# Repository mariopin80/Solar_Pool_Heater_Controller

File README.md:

# Solar Pool Heater Controller

[Português (Brasil)](README.pt-BR.md)

Designed by Mario Pin (PU2PTU). The controller compares water temperatures at the pool and the solar collector and switches the heating pump according to the temperature difference. A separate relay runs the filtration pump on a schedule. Later firmware revisions add manual pump modes, scheduled heating-loop circulation, and a serial Bluetooth interface.

## Hardware

| Board | Controller and clock | Firmware |
| --- | --- | --- |
| [MPS01 1.0](hardware/MPS01/1.0) | ATmega328P at 16 MHz and DS1307 | Historical PCB. This revision reverses SDA and SCL. |
| [MPS01 1.1](hardware/MPS01/1.1) | ATmega328P at 16 MHz and DS1307 | Target board for the archived AVR firmware. Corrected I²C routing. |
| [MPS02 2.0](hardware/MPS02/2.0) | ESP32-WROOM-32D and DS3231M | KiCad design only. This revision stayed at the design stage. |

The MPS01 1.1 is the target for the 13 historical firmware versions and the 0.4.0 beta. The MPS01 uses two 10 kΩ NTC probes, a parallel 16×2 LCD, three push buttons and separate relays for the heating and filtration pumps. The hardware guide includes the Arduino pinout, connector assignments and the sensor-label discrepancy between the MPS01 schematics and sketches. [Hardware and assembly guide](docs/hardware.md) · [Original parts list](docs/BOM.xlsx)

## Firmware

The `v0.4.0-beta` adds a responsive three-button panel, probe and RTC diagnostics, validated EEPROM settings and an optional Bluetooth UART protocol for an app. The MPS01 1.1 pin mapping is unchanged. Download the complete source archive to compile the beta.

- [Beta installation and operating guide](docs/firmware.md)
- [Bluetooth protocol v1](docs/bluetooth.md)
- [Firmware review and commercial feature comparison (PT-BR)](docs/firmware-review.pt-BR.md)
- [Changes by version](CHANGELOG.md)
- [GitHub releases](https://github.com/mariopin80/Aquecedor_piscina/releases)
- [MPS01 PCB test sketch](examples/teste_PCB)

The historical releases retain their original sketches at `firmware/PoolHeater/PoolHeater.ino`. The beta uses that same Arduino entry point with its companion source files in the sketch folder.

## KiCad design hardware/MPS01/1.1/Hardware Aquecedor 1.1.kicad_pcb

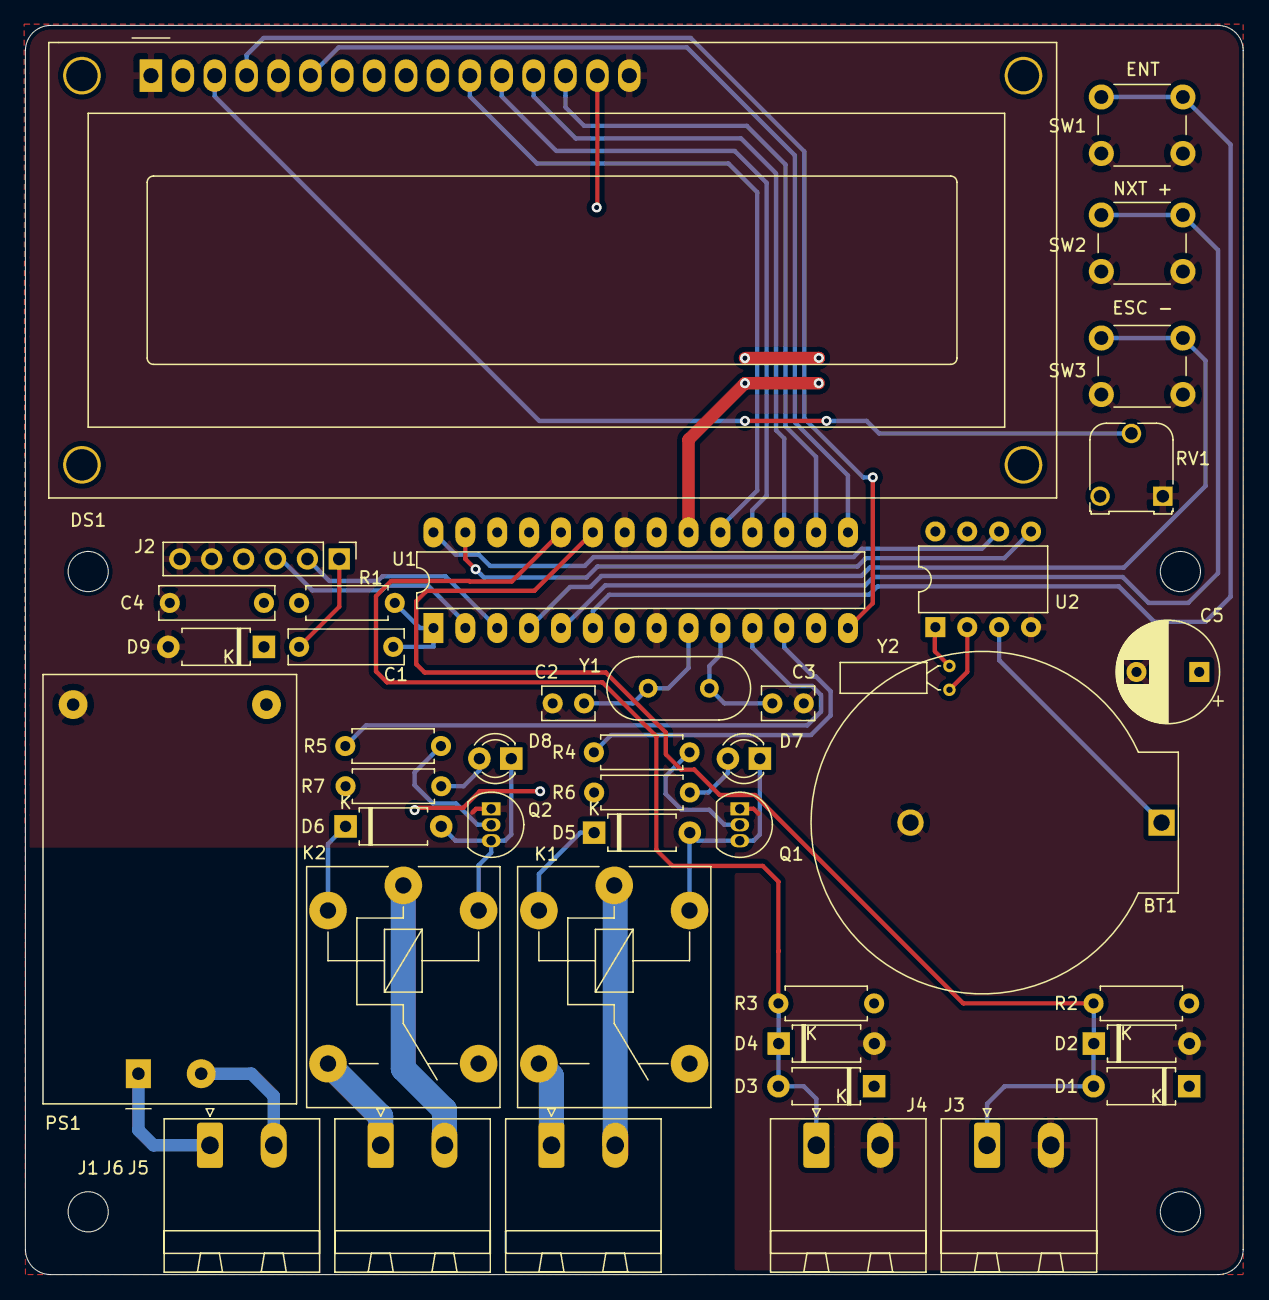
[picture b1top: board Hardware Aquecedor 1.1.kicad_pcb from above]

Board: 2 copper layers, 97.0 x 99.5 mm, 42 parts (0 on the bottom side), 39 nets.

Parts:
BT1: CR2032; BatteryHolder_ComfortableElectronic_CH273-2450_1x2450
C1: 100n; C_Rect_L9.0mm_W2.6mm_P7.50mm_MKT
C2, C3: 20p; C_Rect_L4.0mm_W2.5mm_P2.50mm
C4: 10n; C_Rect_L9.0mm_W2.5mm_P7.50mm_MKT
C5: 100u; CP_Radial_D8.0mm_P5.00mm
D1, D2, D3, D4: 1N4735; D_A-405_P7.62mm_Horizontal
D5, D6: 1N4148; D_A-405_P7.62mm_Horizontal
D7, D8: LED; LED_D3.0mm
D9: D; D_A-405_P7.62mm_Horizontal
DS1: WC1602A
J1: AC 90-240; PhoenixContact_MSTBA_2,5_2-G-5,08_1x02_P5.08mm_Horizontal
J2: FTDI; PinHeader_1x06_P2.54mm_Vertical
J3: CLT; PhoenixContact_MSTBA_2,5_2-G-5,08_1x02_P5.08mm_Horizontal
J4: PSC; PhoenixContact_MSTBA_2,5_2-G-5,08_1x02_P5.08mm_Horizontal
J5: AQC; PhoenixContact_MSTBA_2,5_2-G-5,08_1x02_P5.08mm_Horizontal
J6: FLT; PhoenixContact_MSTBA_2,5_2-G-5,08_1x02_P5.08mm_Horizontal
K1: AQUECEDOR; Relay_SPDT_Finder_36.11
K2: FILTRO; Relay_SPDT_Finder_36.11
PS1: HLK-PM01; Converter_ACDC_HiLink_HLK-PMxx
Q1, Q2: 2N3904; TO-92_Inline
R1, R2, R3, R4, R5: 10k; R_Axial_DIN0207_L6.3mm_D2.5mm_P7.62mm_Horizontal
R6, R7: 330; R_Axial_DIN0207_L6.3mm_D2.5mm_P7.62mm_Horizontal
RV1: 10k; Potentiometer_Runtron_RM-065_Vertical
SW1: ENT; SW_PUSH_6mm
SW2: NXT; SW_PUSH_6mm
SW3: ESC; SW_PUSH_6mm
U1: ATMEGA328PU; DIP-28_W7.62mm_LongPads
U2: DS1307+; DIP-8_W7.62mm
Y1: 16MHz; Crystal_HC49-4H_Vertical
Y2: 32kHz; Crystal_C26-LF_D2.1mm_L6.5mm_Horizontal

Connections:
+5V: C4.1, C5.1, D1.1, D3.1, D5.1, D6.1, D9.1, DS1.2, DS1.15, J2.4, K1.A1, K2.A1, PS1.4, R1.1, R2.1, R3.1, R6.1, R7.1, RV1.3, U1.7, U1.20, U2.8
CLT_TMP: D1.2, D2.1, J3.1, R2.2, U1.23
D4: DS1.11, U1.19
D5: DS1.12, U1.18
D6: DS1.13, U1.17
D7: DS1.14, U1.16
EN: DS1.6, U1.15
GNDREF: BT1.2, C2.1, C3.1, C4.2, C5.2, D2.2, D4.2, D9.2, DS1.1, DS1.5, DS1.16, J2.5, J2.6, J3.2, J4.2, PS1.3, Q1.1, Q2.1, RV1.1, SW1.2, SW2.2, SW3.2, U1.8, U1.22, U2.4
unnamed: BT1.1, U2.3
unnamed: C1.1, J2.1
unnamed: C2.2, U1.9, Y1.1
unnamed: C3.2, U1.10, Y1.2
unnamed: D5.2, D7.1, K1.A2, Q1.3
unnamed: D6.2, D8.1, K2.A2, Q2.3
unnamed: D7.2, R6.2
unnamed: D8.2, R7.2
unnamed: DS1.3, RV1.2
unnamed: J1.1, PS1.1
unnamed: J1.2, PS1.2
unnamed: J5.1, K1.14
unnamed: J5.2, K1.11
unnamed: J6.1, K2.14
unnamed: J6.2, K2.11
unnamed: Q1.2, R4.1
unnamed: Q2.2, R5.1
unnamed: U2.1, Y2.1
unnamed: U2.2, Y2.2
PB1: SW1.1, U1.6
PB2: SW2.1, U1.5
PB3: SW3.1, U1.4
PSC_TMP: D3.2, D4.1, J4.1, R3.2, U1.24
RLY_AQ: R4.2, U1.12
RLY_FL: R5.2, U1.11
RS: DS1.4, U1.14
RTS: C1.2, R1.2, U1.1
RX: J2.3, U1.2
SCL: U1.28, U2.6
SDA: U1.27, U2.5
TX: J2.2, U1.3

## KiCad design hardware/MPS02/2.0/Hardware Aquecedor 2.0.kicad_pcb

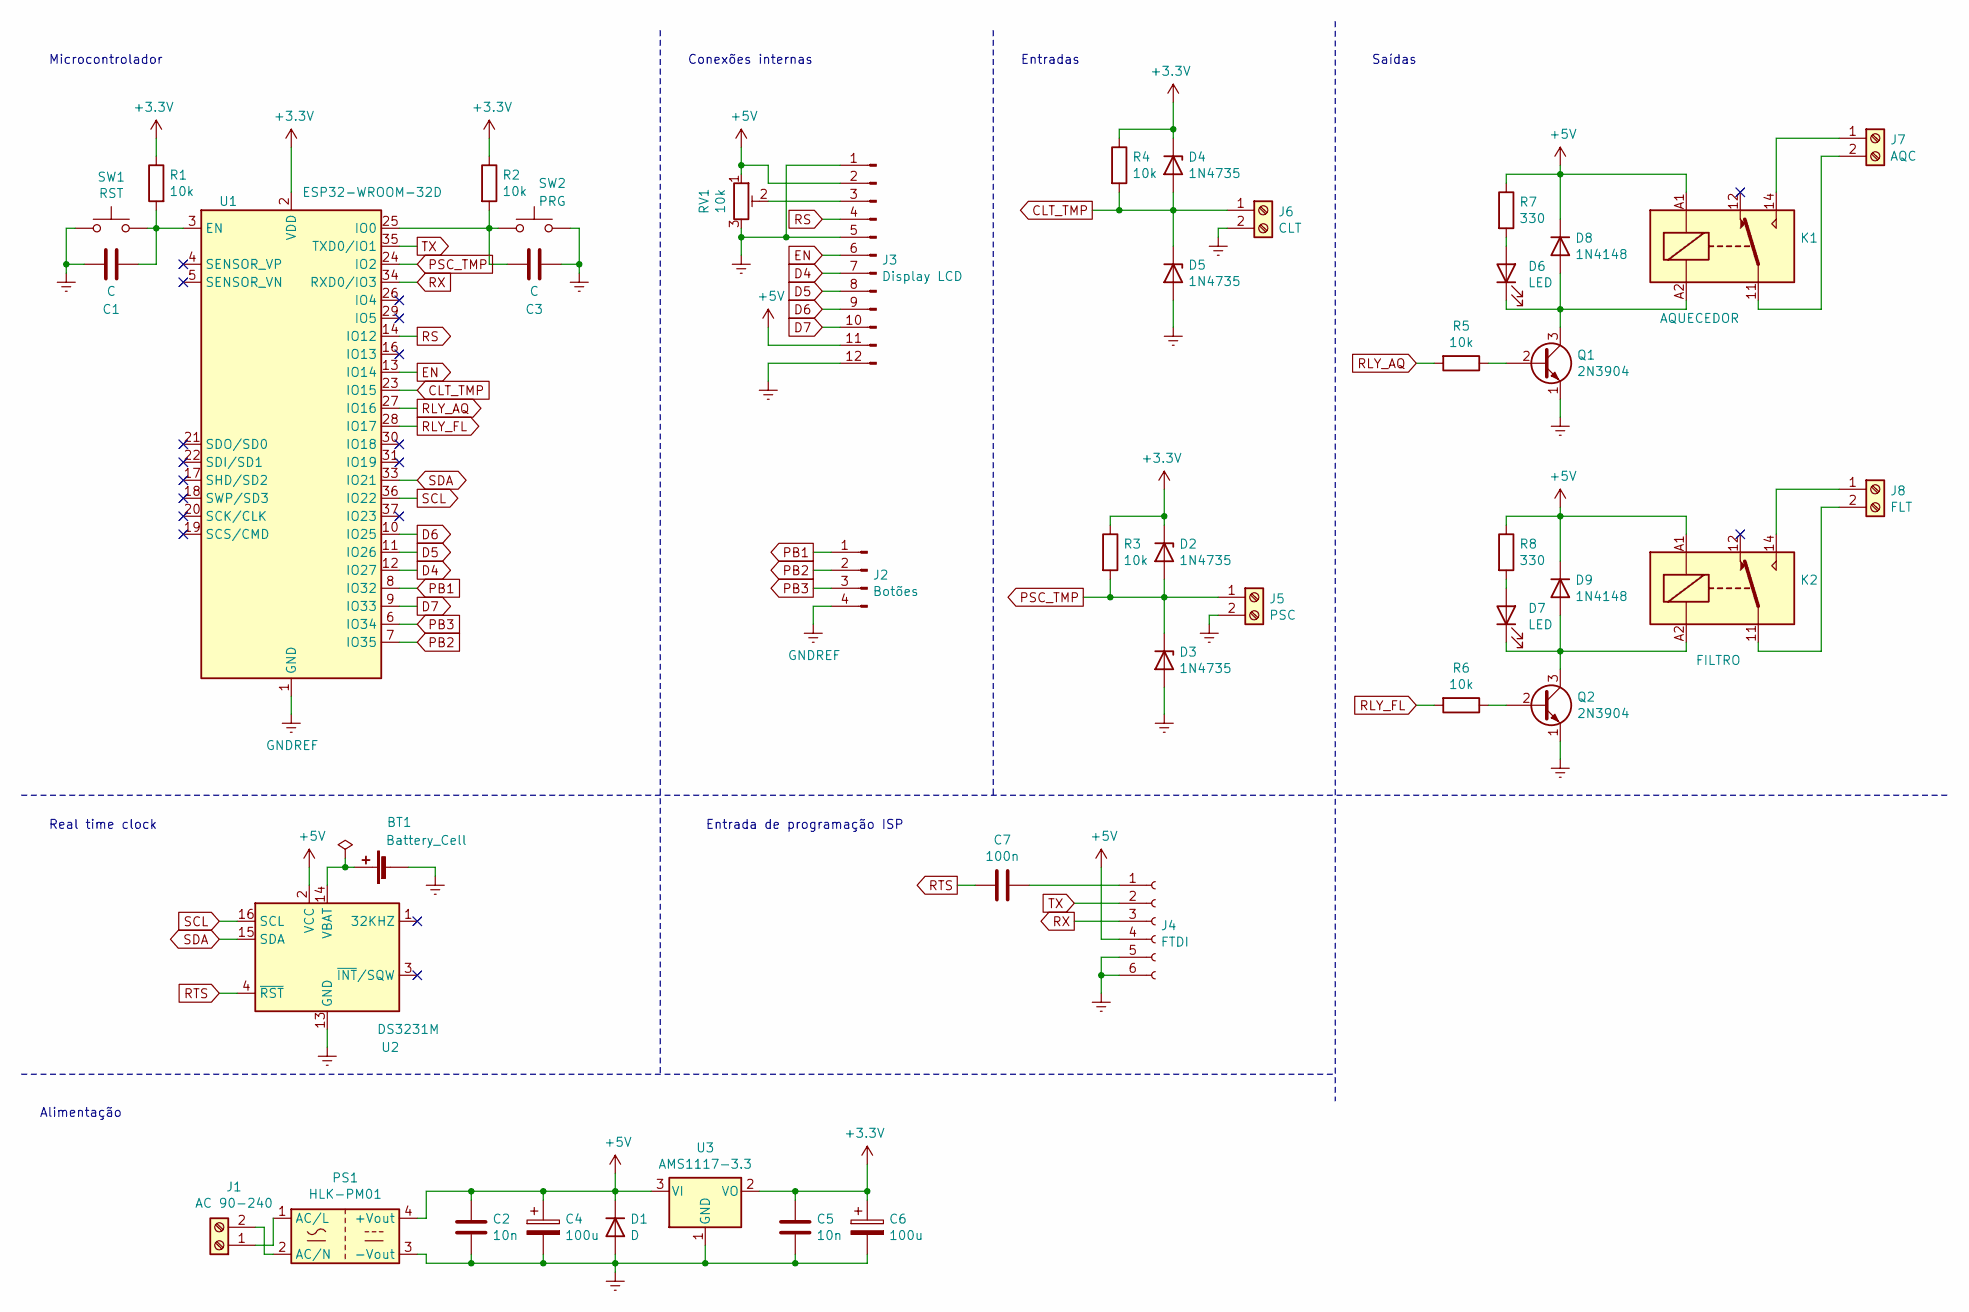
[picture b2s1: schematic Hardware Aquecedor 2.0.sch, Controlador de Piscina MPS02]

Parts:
BT1: Battery_Cell; BatteryHolder_Keystone_103_1x20mm
C1, C3: C; C_0805_2012Metric_Pad1.18x1.45mm_HandSolder
C2, C5: 10n; C_0805_2012Metric_Pad1.18x1.45mm_HandSolder
C4, C6: 100u; CP_Radial_D6.3mm_P2.50mm
C7: 100n; C_0805_2012Metric_Pad1.18x1.45mm_HandSolder
D1: D; D_A-405_P7.62mm_Horizontal
D2, D3, D4, D5: 1N4735; D_A-405_P7.62mm_Horizontal
D6, D7: LED; LED_D3.0mm
D8, D9: 1N4148; D_A-405_P7.62mm_Horizontal
J1: AC 90-240; PhoenixContact_MC_1,5_2-G-5.08_1x02_P5.08mm_Horizontal
J2: Botões; JST_XH_B4B-XH-A_1x04_P2.50mm_Vertical
J3: Display LCD; JST_XH_B12B-XH-A_1x12_P2.50mm_Vertical
J4: FTDI; PinHeader_1x06_P2.54mm_Vertical
J5: PSC; PhoenixContact_MC_1,5_2-G-5.08_1x02_P5.08mm_Horizontal
J6: CLT; PhoenixContact_MC_1,5_2-G-5.08_1x02_P5.08mm_Horizontal
J7: AQC; PhoenixContact_MC_1,5_2-G-5.08_1x02_P5.08mm_Horizontal
J8: FLT; PhoenixContact_MC_1,5_2-G-5.08_1x02_P5.08mm_Horizontal
K1: AQUECEDOR; Relay_SPDT_Finder_36.11
K2: FILTRO; Relay_SPDT_Finder_36.11
PS1: HLK-PM01; Converter_ACDC_HiLink_HLK-PMxx
Q1, Q2: 2N3904; TO-92_Inline
R1, R2, R3, R4, R5, R6: 10k; R_0805_2012Metric_Pad1.20x1.40mm_HandSolder
R7, R8: 330; R_0805_2012Metric_Pad1.20x1.40mm_HandSolder
RV1: 10k; Potentiometer_Runtron_RM-065_Vertical
SW1: RST; SW_PUSH_6mm
SW2: PRG; SW_PUSH_6mm
U1: ESP32-WROOM-32D; ESP32-WROOM-32
U2: DS3231M; SOIC-16W_7.5x10.3mm_P1.27mm
U3: AMS1117-3.3; SOT-223-3_TabPin2

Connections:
+3V3: C5.1, C6.1, D2.1 (K), D4.1 (K), R1.1, R2.1, R3.1, R4.1, U1.2 (VDD), U3.2 (VO)
+5V: C2.1, C4.1, D1.1 (K), D8.1 (K), D9.1 (K), J3.2, J3.11, J4.4, K1.A1, K2.A1, PS1.4 (+Vout), R7.1, R8.1, RV1.1, U2.2 (VCC), U3.3 (VI); also elsewhere on the board
CLT_TMP: D4.2 (A), D5.1 (K), J6.1, R4.2, U1.23 (IO15)
D4: J3.7, U1.12 (IO27); also elsewhere on the board
D5: J3.8, U1.11 (IO26); also elsewhere on the board
D6: J3.9, U1.10 (IO25); also elsewhere on the board
D7: J3.10, U1.9 (IO33); also elsewhere on the board
EN: J3.6, U1.13 (IO14); also elsewhere on the board
GNDREF: BT1.2 (-), C1.1, C2.2, C3.1, C4.2, C5.2, C6.2, D1.2 (A), D3.2 (A), D5.2 (A), J2.4, J3.1, J3.5, J3.12, J4.5, J4.6, J5.2, J6.2, PS1.3 (-Vout), Q1.1 (E), Q2.1 (E), RV1.3, SW1.2, SW2.2, U1.1 (GND), U1.15 (GND), U1.38 (GND), U1.39 (GND), U2.5 (GND), U2.6 (GND), U2.7 (GND), U2.8 (GND), U2.9 (GND), U2.10 (GND), U2.11 (GND), U2.12 (GND), U2.13 (GND), U3.1 (GND); also elsewhere on the board
unnamed: BT1.1 (+), U2.14 (VBAT)
unnamed 10: C1.2, R1.2, SW1.1, U1.3 (EN); also elsewhere on the board
unnamed 11: C3.2, R2.2, SW2.1, U1.25 (IO0); also elsewhere on the board
unnamed: C7.1, J4.1
unnamed: D6.1 (K), D8.2 (A), K1.A2, Q1.3 (C)
unnamed: D6.2 (A), R7.2
unnamed: D7.1 (K), D9.2 (A), K2.A2, Q2.3 (C)
unnamed: D7.2 (A), R8.2
unnamed: J1.1, PS1.1 (AC/L)
unnamed: J1.2, PS1.2 (AC/N)
unnamed 19: J3.3, RV1.2; also elsewhere on the board
unnamed: J7.1, K1.14
unnamed: J7.2, K1.11
unnamed: J8.1, K2.14
unnamed: J8.2, K2.11
unnamed: Q1.2 (B), R5.1
unnamed: Q2.2 (B), R6.1
PB1: J2.1, U1.8 (IO32); also elsewhere on the board
PB2: J2.2, U1.7 (IO35); also elsewhere on the board
PB3: J2.3, U1.6 (IO34); also elsewhere on the board
PSC_TMP: D2.2 (A), D3.1 (K), J5.1, R3.2, U1.24 (IO2)
RLY_AQ: R5.2, U1.27 (IO16)
RLY_FL: R6.2, U1.28 (IO17)
RS: J3.4, U1.14 (IO12); also elsewhere on the board
RTS: C7.2, U2.4 (~RST)
RX: J4.3, U1.34 (RXD0/IO3)
SCL: U1.36 (IO22), U2.16 (SCL)
SDA: U1.33 (IO21), U2.15 (SDA)
TX: J4.2, U1.35 (TXD0/IO1)

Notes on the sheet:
Microcontrolador
Entradas
Saídas
Entrada de programação ISP
Real time clock
Conexões internas
Alimentação

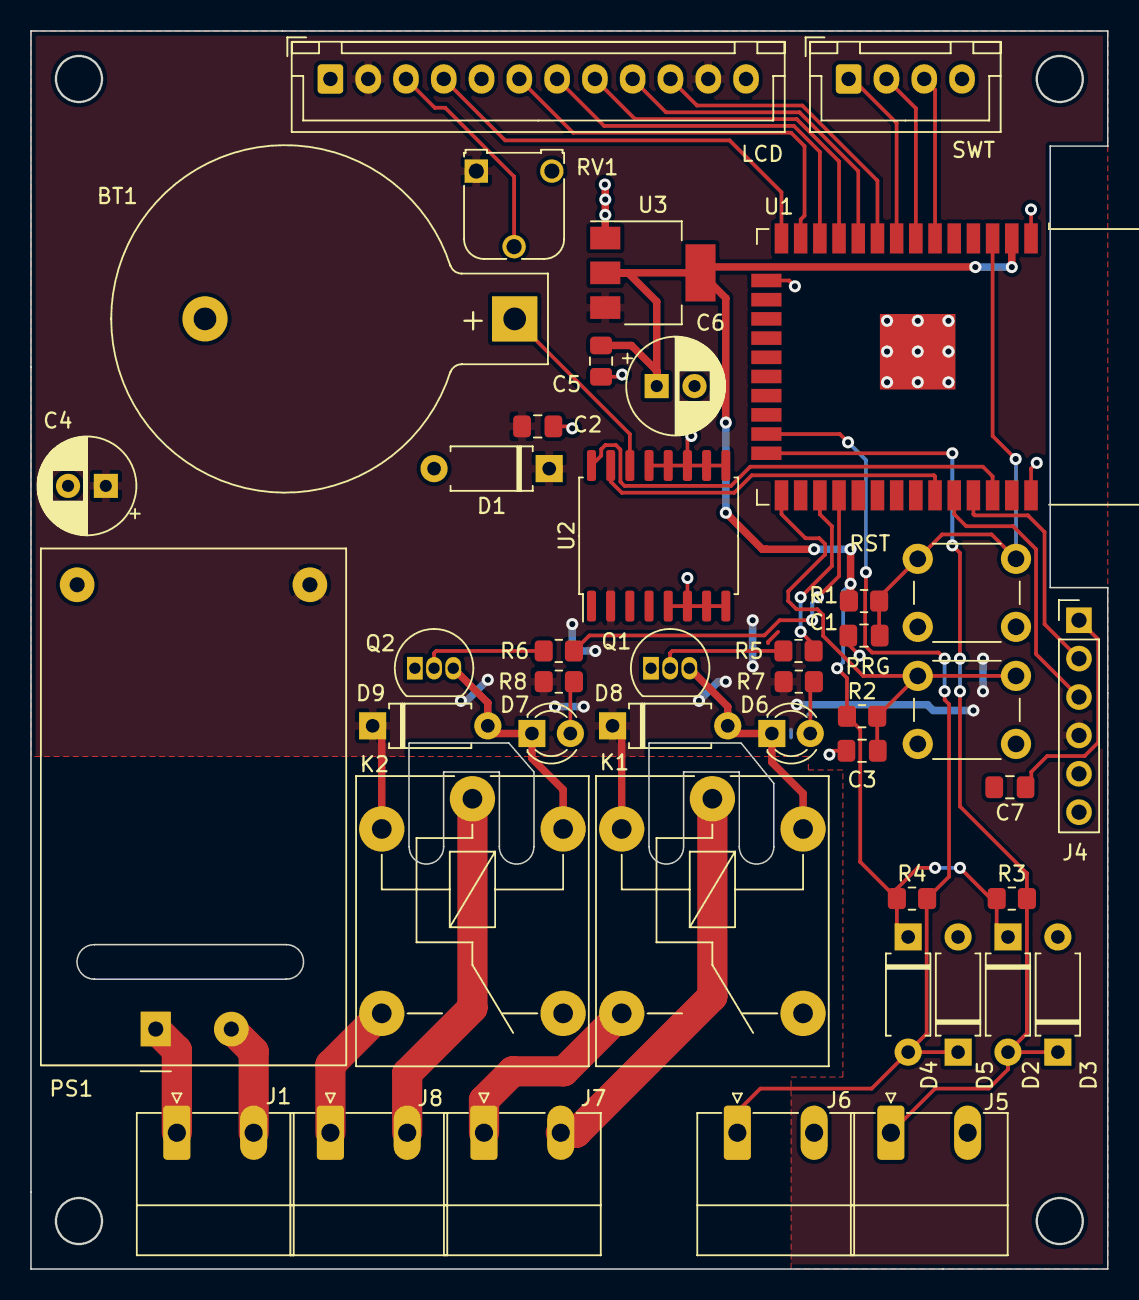
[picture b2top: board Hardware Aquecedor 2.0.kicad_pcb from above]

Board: 2 copper layers, 71.2 x 81.9 mm, 44 parts (0 on the bottom side), 38 nets.

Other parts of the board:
LCD: Display LCD; JST_XH_B12B-XH-A_1x12_P2.50mm_Vertical
PRG: PRG; SW_PUSH_6mm
RST: RST; SW_PUSH_6mm
SWT: Botões; JST_XH_B4B-XH-A_1x04_P2.50mm_Vertical

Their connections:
+5V: LCD.2, LCD.11; also elsewhere on the board
D4: LCD.7; also elsewhere on the board
D5: LCD.8; also elsewhere on the board
D6: LCD.9; also elsewhere on the board
D7: LCD.10; also elsewhere on the board
EN: LCD.6; also elsewhere on the board
GNDREF: LCD.1, LCD.5, LCD.12, PRG.2, RST.2, SWT.4; also elsewhere on the board
unnamed 10: RST.1; also elsewhere on the board
unnamed 11: PRG.1; also elsewhere on the board
unnamed 19: LCD.3; also elsewhere on the board
PB1: SWT.1; also elsewhere on the board
PB2: SWT.2; also elsewhere on the board
PB3: SWT.3; also elsewhere on the board
RS: LCD.4; also elsewhere on the board
